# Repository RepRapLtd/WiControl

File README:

Wireless Home/Building Control System
=====================================

Adrian Bowyer
RepRap Ltd
https://reprapltd.com

Licence: GPL

This is a system for controlling devices in buildings (primarily, but not exclusively, heating; it will also do lighting and other things) with a web interface.  It is fully open-source and free.  The licence is the GPL.

There are two versions:

  1. Raspberry Pi + PanStamp in the directory PanStamp. This has been working for a few years, and is now frozen and will not be developed further.

  2. WiFi based on the ESP-8266 in the directory ESP-8266.  This is in development.

Both start with a php script that serves web pages where you can edit, for example, temperature profiles for individual rooms.  That data is saved in files on the server.

The ESP-8266s (or Pi) then get that data and decide(s) what to turn on and off.

More documentation needs to be written...

More importantly, security is minimal and needs to be properly implemented.

See also (for homemade solenoid valves): https://www.thingiverse.com/thing:3496770

WiControl - ESP-8266
====================

This version does everything that the PanStamp version did, but more simply and robustly (the robustness has nothing to do with the hardware change; the PanStamps are fine; it has to do with a simplification of the protocols and hardware).

This version of the system will also support Google Home and Amazon Echo/Alexa.

Some more instructions here would be a good idea...

WiControl - Raspberry Pi + PanStamp
===================================

This allows temperature profiles to be set for each individual room for all times of the day and every day of the week.

It can be controlled using a web browser from anywhere.

It uses Panstamps (http://www.panstamp.com/) for the individual rooms and a Raspberry Pi (https://www.raspberrypi.org/) as the main building controller.

This repository contains all the software and all the hardware designs.

One thing it lacks is full documentation, as I created it for my own use and I know how it works.  Sorry.

Installation:
-------------

On the Pi:

This assumes you have an out-of-the-box Raspberry Pi SD card with no extra software installed.

First set your local timezone:

$ sudo dpkg-reconfigure tzdata

You may want to change the default name of the Pi ("raspberrypi") to something more appropriate 
like "heatingcontrol".  To do that:

$ sudo nano /etc/hostname

That file contains a single name - the name of the Pi.  Change it to what you want, save the file, then reboot.

Change you password:

$ passwd

And enable ssh:

$ sudo raspi-config

Next install Apache and PHP:

$ sudo apt-get update
$ sudo apt-get install apache2 -y
$ sudo apt-get install php5 libapache2-mod-php5 -y

At this point it is a good idea to check that the webserver is now running.  In the URL address bar of a web browser on a PC or phone type

  myname.home/

where myname is the Pi's name that you created above (some networks need myname.local instead).  If you don't get anything type 

$ ifconfig

on the Pi.  This will tell you the Pi's IP address (something like 192.168.1.163).  Type that IP address into the web browser's URL bar.  You should see the default Apache/Debian server homepage.

Next install ftp:

$ sudo apt-get install ftp

And the ftp demon:

$ sudo apt-get install pure-ftpd

Create an ftp user (see https://www.raspberrypi.org/documentation/remote-access/ftp.md) called "upload" with access to the html directory:

$ sudo groupadd ftpgroup
$ sudo useradd ftpuser -g ftpgroup -s /sbin/nologin -d /dev/null
$ pushd /var/www/html/
$ sudo chown -R ftpuser:ftpgroup .
$ sudo pure-pw useradd upload -u ftpuser -g ftpgroup -d /var/www/html -m
[** You will be asked to create a password for the user upload at this point**]
$ sudo pure-pw mkdb
$ sudo ln -s /etc/pure-ftpd/conf/PureDB /etc/pure-ftpd/auth/60puredb
$ sudo service pure-ftpd restart
$ popd

You next need to install the heating software:

$ git clone https://github.com/RepRapLtd/WiControl.git
$ cd WiControl/PanStamp

Copy the control file:

$ cp run-heat-control.sample run-heat-control

and edit the file run-heat-control and replace the "zone-1"s with the name of the zone you want.

Copy the sending file:

$ cp sendtemps.sample sendtemps

and edit the sendtemps file to include the ftp password you set above and to change zone-1 to the name of your zone.

Backup the webserver's index file, and copy all the heating web files there and set permissions:

$ sudo mv /var/www/html/index.html /var/www/html/index.html.old
$ cd Web
$ sudo cp -r * /var/www/html
$ sudo chown -R ftpuser:ftpgroup /var/www/html
$ sudo chmod 666 /var/www/html/*.dat
$ sudo chmod 777 /var/www/html/zone-1-Profiles

Finally

$ sudo crontab -e

and add a line at the end like this:

* * * * * /home/pi/WiControl/run-heat-control

That will cause the shell script run-heat-control to be run once a minute.

On the PanStamps:

You can just about run the Arduino IDE on the Raspberry Pi, but it's probably better to
use a big serious computer to do this bit.  Install the Arduino IDE on your computer if
you haven't already got it:

https://www.arduino.cc/en/Main/Software

And clone the repository https://github.com/RepRapLtd/WiControl.git as you did on the Pi.

Load the arduino program in the folder Panstamp-control into the IDE.

At the head of the file Control.h set up your heating zones and device names and numbers.  Load 
this program into each device (e.g. boiler, radiator) on your heating system.

Running
-------

When it runs it creates a status file called Status.

$ cat Status

will tell you what your system last did.  If you

$ touch Log

then each time run-heat-control runs it will append the status
report to the end of itself, which keeps a history and is therefore
useful for debugging.

When you have finished debugging don't forget to

$ rm Log

otherwise it will eventually fill up the SD/disc...

Adrian Bowyer

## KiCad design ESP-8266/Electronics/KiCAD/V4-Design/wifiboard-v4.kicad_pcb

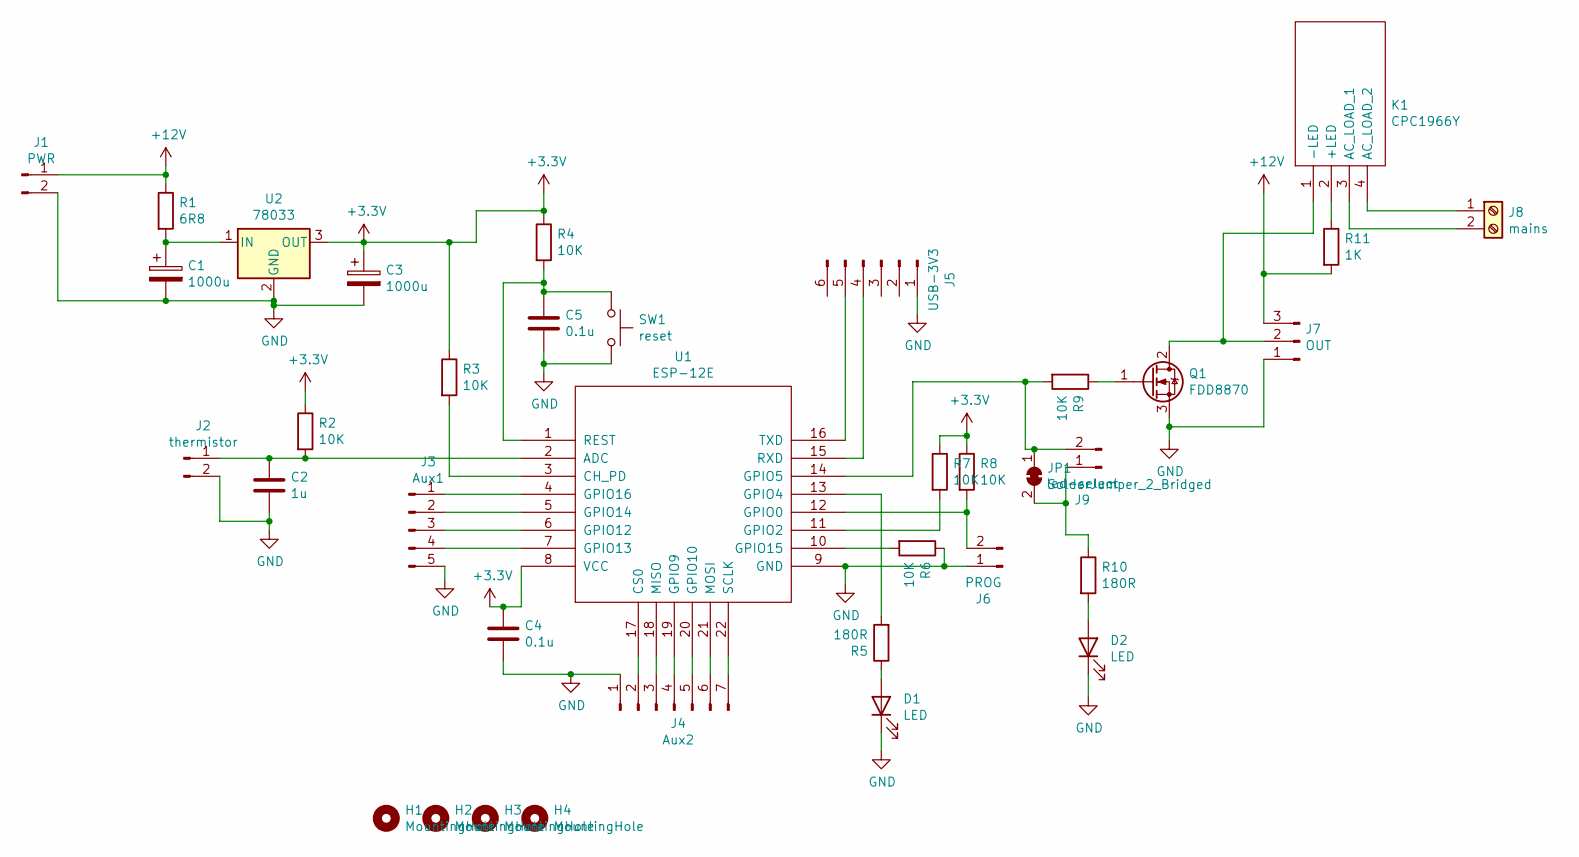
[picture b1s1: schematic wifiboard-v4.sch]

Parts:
C1, C3: 1000u; CP_Radial_D10.0mm_P5.00mm
C2: 1u; C_0805_2012Metric
C4, C5: 0.1u; C_0805_2012Metric
D1, D2: LED; LED_D3.0mm
H1, H2, H3, H4: MountingHole; MountingHole_2.5mm
J1: PWR; PinHeader_1x02_P2.54mm_Vertical
J2: thermistor; PinHeader_1x02_P2.54mm_Vertical
J3: Aux1; PinHeader_1x05_P2.54mm_Vertical
J4: Aux2; PinHeader_1x07_P2.54mm_Vertical
J5: USB-3V3; PinHeader_1x06_P2.54mm_Vertical
J6: PROG; PinHeader_1x02_P2.54mm_Vertical
J7: OUT; PinHeader_1x03_P2.54mm_Vertical
J8: mains; TerminalBlock_bornier-2_P5.08mm
J9: led-select; PinHeader_1x02_P2.54mm_Vertical
JP1: SolderJumper_2_Bridged; SolderJumper-2_P1.3mm_Bridged_RoundedPad1.0x1.5mm
K1: CPC1966Y; Manufacturer_Part_Number CPC1966Y; Mouser Part Number 849-CPC1966Y
Q1: FDD8870; TO-252-2
R1: 6R8; R_Axial_DIN0414_L11.9mm_D4.5mm_P15.24mm_Horizontal
R2, R3, R4, R6, R7, R8, R9: 10K; R_0805_2012Metric
R5, R10: 180R; R_0805_2012Metric
R11: 1K; R_0805_2012Metric
SW1: reset; SW_SPST_TL3342
U1: ESP-12E
U2: 78033; TO-252-2

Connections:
+3V3: C3.1, C4.1, R2.1, R3.1, R4.1, R7.1, R8.1, U1.8 (VCC), U2.3 (OUT)
+12V: J1.1, J7.3, R1.1, R11.2
GND: C1.2, C2.2, C3.2, C4.2, C5.2, D1.1 (K), D2.1 (K), J1.2, J2.2, J3.5, J4.1, J5.1, J6.1, J7.1, Q1.3 (S), R6.1, SW1.2, U1.9 (GND), U2.2 (GND)
unnamed: C1.1, R1.2, U2.1 (IN)
unnamed: C2.1, J2.1, R2.2, U1.2 (ADC)
unnamed: C5.1, R4.2, SW1.1, U1.1 (REST)
unnamed: D1.2 (A), R5.1
unnamed: D2.2 (A), R10.2
unnamed: J3.1, U1.4 (GPIO16)
unnamed: J3.2, U1.5 (GPIO14)
unnamed: J3.3, U1.6 (GPIO12)
unnamed: J3.4, U1.7 (GPIO13)
unnamed: J4.2, U1.17 (CS0)
unnamed: J4.3, U1.18 (MISO)
unnamed: J4.4, U1.19 (GPIO9)
unnamed: J4.5, U1.20 (GPIO10)
unnamed: J4.6, U1.21 (MOSI)
unnamed: J4.7, U1.22 (SCLK)
unnamed: J5.4, U1.15 (RXD)
unnamed: J5.5, U1.16 (TXD)
unnamed: J6.2, R8.2, U1.12 (GPIO0)
unnamed: J7.2, K1.1 (-LED), Q1.2 (D)
unnamed: J8.1, K1.4 (AC_LOAD_2)
unnamed: J8.2, K1.3 (AC_LOAD_1)
unnamed: J9.1, JP1.2 (B), R10.1
unnamed: J9.2, JP1.1 (A), R9.2, U1.14 (GPIO5)
unnamed: K1.2 (+LED), R11.1
unnamed: Q1.1 (G), R9.1
unnamed: R3.2, U1.3 (CH_PD)
unnamed: R5.2, U1.13 (GPIO4)
unnamed: R6.2, U1.10 (GPIO15)
unnamed: R7.2, U1.11 (GPIO2)

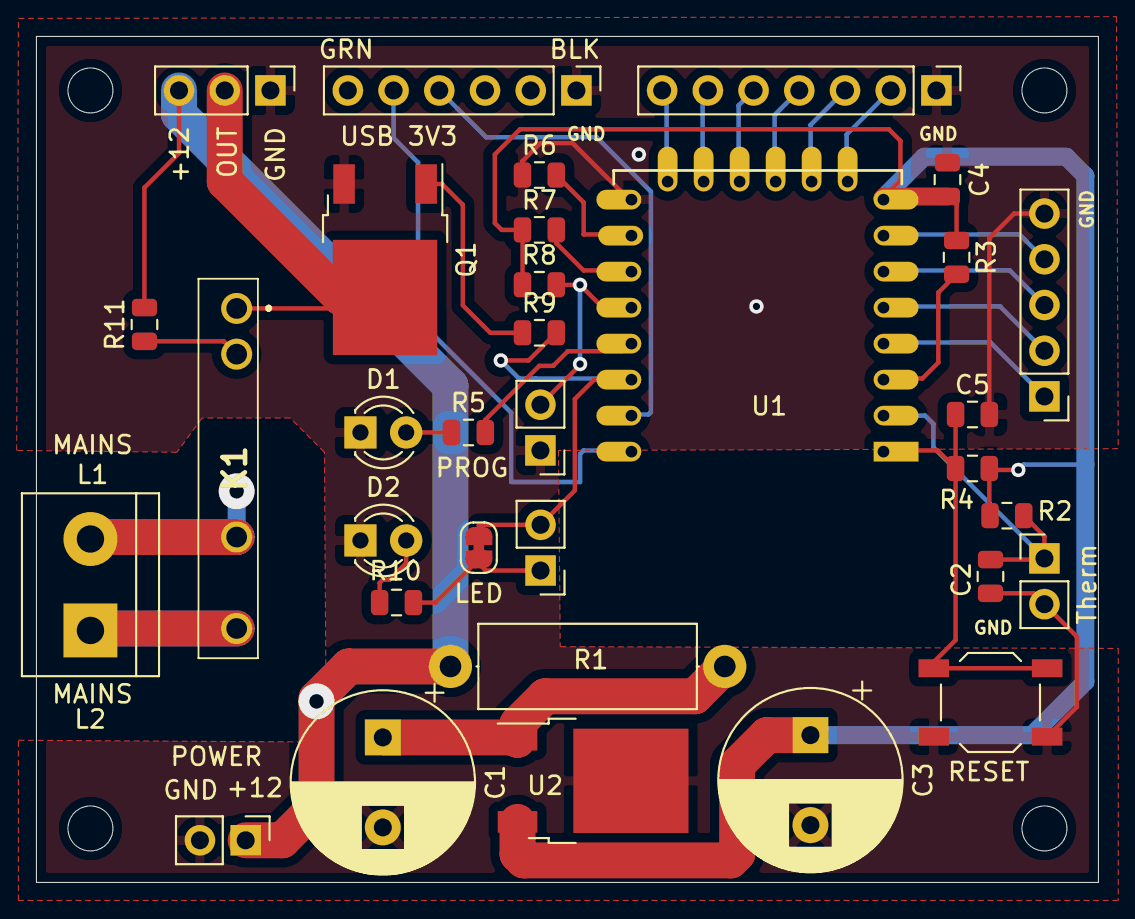
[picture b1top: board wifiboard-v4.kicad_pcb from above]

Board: 2 copper layers, 59.0 x 47.0 mm, 37 parts (0 on the bottom side), 32 nets.

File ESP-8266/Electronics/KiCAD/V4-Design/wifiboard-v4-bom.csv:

Reference, Value, Footprint, Datasheet, Arrow Part Number, Arrow Price/Stock, Description, Height, Manufacturer_Name, Manufacturer_Part_Number, Mouser Part Number, Mouser Price/Stock
"J5","USB-3V3","Connector_PinHeader_2.54mm:PinHeader_1x06_P2.54mm_Vertical","~"
"J3","Aux1","Connector_PinHeader_2.54mm:PinHeader_1x05_P2.54mm_Vertical","~"
"J4","Aux2","Connector_PinHeader_2.54mm:PinHeader_1x07_P2.54mm_Vertical","~"
"C4","0.1u","Capacitor_SMD:C_0805_2012Metric","~"
"J2","thermistor","Connector_PinHeader_2.54mm:PinHeader_1x02_P2.54mm_Vertical","~"
"C2","1u","Capacitor_SMD:C_0805_2012Metric","~"
"R2","10K","Resistor_SMD:R_0805_2012Metric","~"
"R3","10K","Resistor_SMD:R_0805_2012Metric","~"
"C5","0.1u","Capacitor_SMD:C_0805_2012Metric","~"
"R4","10K","Resistor_SMD:R_0805_2012Metric","~"
"SW1","reset","Button_Switch_SMD:SW_SPST_TL3342","~"
"R1","6R8","Resistor_THT:R_Axial_DIN0414_L11.9mm_D4.5mm_P15.24mm_Horizontal","~"
"J1","PWR","Connector_PinHeader_2.54mm:PinHeader_1x02_P2.54mm_Vertical","~"
"C1","1000u","Capacitor_THT:CP_Radial_D10.0mm_P5.00mm","~"
"C3","1000u","Capacitor_THT:CP_Radial_D10.0mm_P5.00mm","~"
"J6","PROG","Connector_PinHeader_2.54mm:PinHeader_1x02_P2.54mm_Vertical","~"
"R8","10K","Resistor_SMD:R_0805_2012Metric","~"
"R6","10K","Resistor_SMD:R_0805_2012Metric","~"
"R7","10K","Resistor_SMD:R_0805_2012Metric","~"
"R9","10K","Resistor_SMD:R_0805_2012Metric","~"
"D1","LED","LED_THT:LED_D3.0mm","~"
"R5","180R","Resistor_SMD:R_0805_2012Metric","~"
"U1","ESP-12E","esp-8266:ESP-12E","http://l0l.org.uk/2014/12/esp8266-modules-hardware-guide-got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"
"D2","LED","LED_THT:LED_D3.0mm","~"
"R10","180R","Resistor_SMD:R_0805_2012Metric","~"
"J7","OUT","Connector_PinHeader_2.54mm:PinHeader_1x03_P2.54mm_Vertical","~"
"K1","CPC1966Y","reprapltd-kicad:CPC1966Y","https://datasheet.datasheetarchive.com/originals/distributor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","CPC1966Y","https://www.arrow.com/en/products/cpc1966y/ixys","IXYS 3 A rms SPNO Solid State Relay, Zero Crossing, PCB Mount SCR, 240 V ac Maximum Load","10","LITTELFUSE","CPC1966Y","849-CPC1966Y","https://www.mouser.co.uk/ProductDetail/IXYS-Integrated-Circu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"
"R11","1K","Resistor_SMD:R_0805_2012Metric","~"
"J8","mains","TerminalBlock:TerminalBlock_bornier-2_P5.08mm","~"
"Q1","FDD8870","Package_TO_SOT_SMD:TO-252-2","http://www.jaolen.com/images/pdf/QM6006D.pdf"
"H4","MountingHole","MountingHole:MountingHole_2.5mm","~"
"H3","MountingHole","MountingHole:MountingHole_2.5mm","~"
"H2","MountingHole","MountingHole:MountingHole_2.5mm","~"
"H1","MountingHole","MountingHole:MountingHole_2.5mm","~"
"J9","led-select","Connector_PinHeader_2.54mm:PinHeader_1x02_P2.54mm_Vertical","~"
"U2","78033","Package_TO_SOT_SMD:TO-252-2","http://www.st.com/content/ccc/resource/technical/document/da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"
"JP1","SolderJumper_2_Bridged","Jumper:SolderJumper-2_P1.3mm_Bridged_RoundedPad1.0x1.5mm","~"

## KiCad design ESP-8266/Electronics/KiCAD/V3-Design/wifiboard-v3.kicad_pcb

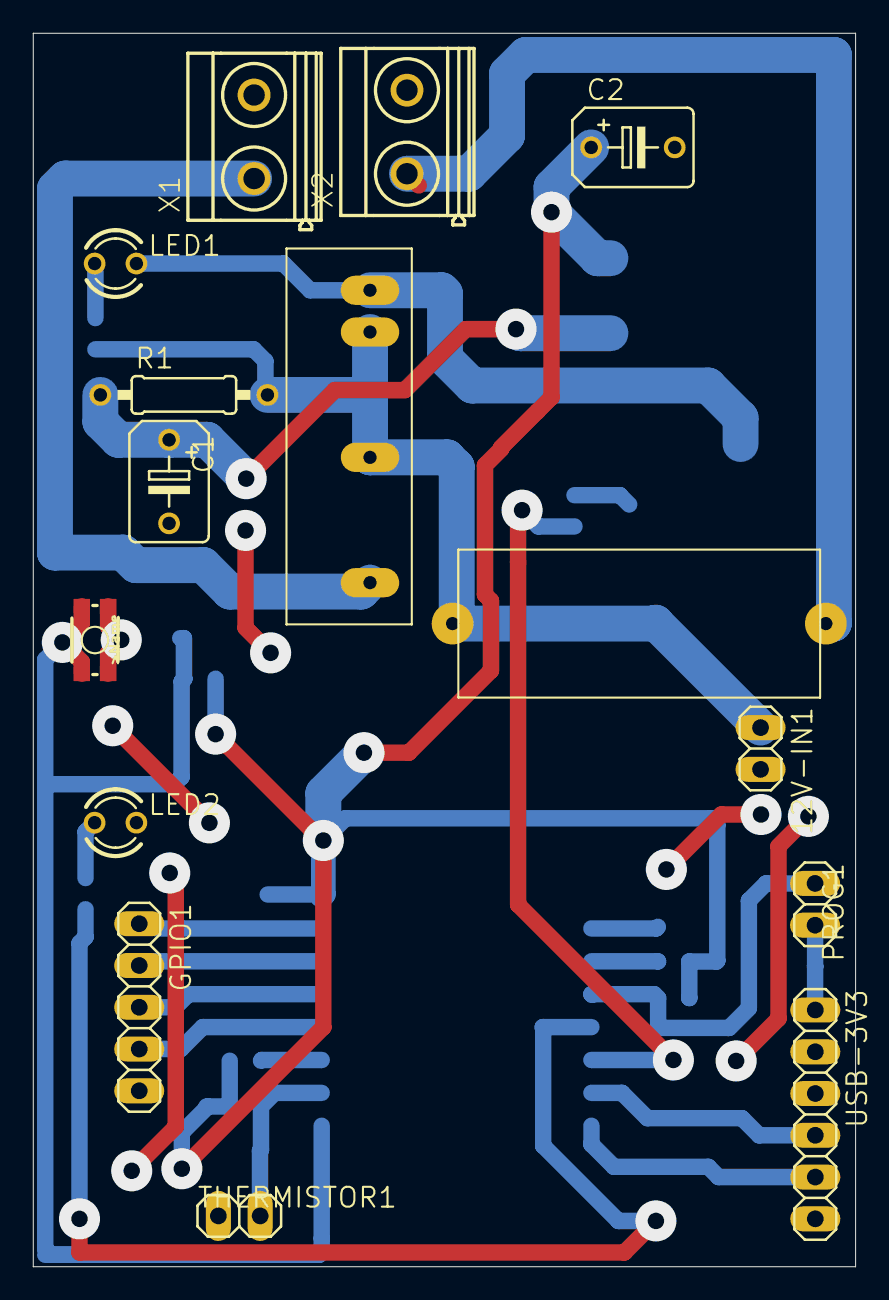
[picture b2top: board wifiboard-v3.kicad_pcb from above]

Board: 2 copper layers, 50.0 x 75.0 mm, 30 parts (0 on the bottom side), 24 nets.

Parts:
12V-IN1: PINHD-1X2; 1X02
C1, C2: 1000uF; B45181B
C3: 1uF; C0805
C5, C6: 0.1u; C0805
FUSE1: FUSE
GPIO1: PINHD-1X5; 1X05
IC2: 78033AF; TO252
LED1, LED2: LED3MM
PROG1: PINHD-1X2; 1X02
Q1: FDD8870; DPAK
R1: 6R8; 0207_10
R2, R3: 10K; M0805
R4, R5, R6, R7, R8: 10K; R0805
R9: 1K; R0805
R10: 180R; R0805
RESET1: TACTILE_SWITCH_SMD_4.6X2.8MM
RLA1: OMRON-G6DN; OMRON-G6DN-1A
THERMISTOR1: PINHD-1X2; 1X02
U2: ESP12ESMD; ESP12E-SMD
USB-3V3: PINHD-1X6; 1X06
X1: AC-N; MKDSN1,5_2-5,08
X2: AC-L; MKDSN1,5_2-5,08

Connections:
+3V3: C2.+, C5.1, IC2.2, R2.1, R4.2, R5.2, R7.2, R8.2, U2.VCC
+12V: 12V-IN1.1, FUSE1.P$1, R1.2, R9.2, RLA1.P$2, RLA1.P$3
GND: 12V-IN1.2, C1.-, C2.-, C3.2, C5.2, C6.2, GPIO1.5, IC2.3, LED2.K, PROG1.2, Q1.3, R6.1, RESET1.3, RESET1.4, THERMISTOR1.1, U2.GND, USB-3V3.1, X1.2, X2.2
unnamed: C1.+, IC2.1, R1.1
unnamed: C3.1, R2.2, THERMISTOR1.2, U2.ADC
unnamed: C6.1, R4.1, RESET1.1, RESET1.2, U2.RESET
unnamed: FUSE1.P$2, X2.1
unnamed: GPIO1.1, U2.GPIO13
unnamed: GPIO1.2, U2.GPIO12
unnamed: GPIO1.3, U2.GPIO14
unnamed: GPIO1.4, U2.GPIO16
unnamed: LED1.A, R9.1
unnamed: LED1.K, Q1.4, RLA1.P$1
unnamed: LED2.A, R10.1
unnamed: PROG1.1, R5.1, U2.GPIO0
unnamed: Q1.1, R3.1
unnamed: R3.2, U2.GPIO5
unnamed: R6.2, U2.GPIO15
unnamed: R7.1, U2.CH_PD
unnamed: R8.1, U2.GPIO2
unnamed: R10.2, U2.GPIO4
unnamed: RLA1.P$4, X1.1
unnamed: U2.RXD0, USB-3V3.4
unnamed: U2.TXD0, USB-3V3.5

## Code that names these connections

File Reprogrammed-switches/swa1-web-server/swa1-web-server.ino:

/*

SWA1 Smart Switch Web Server

This turns a SWA1 smart switch into a web server on your network. You can
then load the page it serves in a browser on your PC or phone and turn 
the switch on or off from that page.

RepRap Ltd
https://reprapltd.com


Written by GPT4 (code) and Adrian Bowyer (comments)

3 May 2024

Licence: GPL


**** UNPLUG THE SMART SWITCH FROM THE MAINS FOR ALL BUT THE VERY END OF THIS. ****


Select "Generic ESP8266 Module" from the Arduino IDE Boards menu.

Open the Arduino IDE serial monitor and set the speed to 74880 baud.

Edit the code below to put your network's WiFi SSID and password in.

Dismantle the smart switch (5 Phillips screws on mine). 

The SWA1 Smart Switch has an ESP8266 internally which you can access
through a 5-pin connector on its PCB. (You may have to solder that connector in - it's 
not fitted on all devices.)

The pins are (counting pin 1 as the pin nearest the edge of the PCB):

Pin   GPIO    Function

1     3       Rx (recieve)
2     1       Tx (transmit)
3     -       GND (0v)
4     0       hold 0 to program on power up
5     -       Vdd (+3v3)

Internally, the LED is on GPIO4, the mains relay is on GPIO5 and the push button
grounds GPIO13.   

To program it from the Arduino IDE you will need a TTL-232R-3v3 USB cable.

Connect that as follows

SWA1      TTL-232R-3v3

Rx        Tx (Orange)
Tx        Rx (Yellow)
GND       GND (Black)
GPIO0     RTS (Green)
Vdd       3v3 (Red)

Puting a normally-closed push button in the power (3v3) line will make things
easier. You have to cycle the power as the Arduino IDE starts to program the device.
The sequence is that the IDE compiles the code then pulls RTS low. The ESP8266 has
to be rebooted then to put it in programming mode, so you push the switch for a second
when the IDE says it's trying to connect. You won't get the timing right every go, but it 
usually works. If you don't catch it, the ESP8266 just retains whatever firmware was in
it before. Try again.

When the IDE has completely finished programming the device (don't do this too early) you can
can reboot the ESP8266 by cycling its power again. It should then give a series of dots as it connects 
to your network and then tell you the IP address it's been allocated.

Put that IP address into a web browser and you will get a page that allows you to
turn the switch on and off. Pushing the button on the front of the switch achieves
the same.

Tell your internet hub to always use that IP address for the device then put it
all back together. Plug it into a socket and you have a web-page-controlled mains switch.


*/


#include <ESP8266WiFi.h>
#include <ESP8266WebServer.h>

const char* ssid = "MY_SSID";
const char* password = "my_password";

ESP8266WebServer server(80);

// Pin definitions
const int relayPin = 5;
const int buttonPin = 13;
const int ledPin = 4;

// Variable to store the relay state
bool relayState = false;

void setup() {
  Serial.begin(74880);
  pinMode(relayPin, OUTPUT);
  pinMode(buttonPin, INPUT_PULLUP); // Set button input mode
  pinMode(ledPin, OUTPUT);

  // Initialize relay and LED state
  digitalWrite(relayPin, relayState);
  digitalWrite(ledPin, relayState);

  WiFi.begin(ssid, password);
  Serial.println("");

  // Wait for connection
  while (WiFi.status() != WL_CONNECTED) {
    delay(500);
    Serial.print(".");
  }
  Serial.println("");
  Serial.print("Connected to ");
  Serial.println(ssid);
  Serial.print("IP address: ");
  Serial.println(WiFi.localIP());

  // Define server routes
  server.on("/", handleRoot);
  server.on("/toggle", handleToggle);

  server.begin();
  Serial.println("HTTP server started");
}

void loop() {
  server.handleClient();
  checkButton();
}

void checkButton() {
  static bool lastButtonState = HIGH;
  bool currentButtonState = digitalRead(buttonPin);
  if (lastButtonState == HIGH && currentButtonState == LOW) {
    // Button is pressed; toggle the relay
    relayState = !relayState;
    digitalWrite(relayPin, relayState);
    digitalWrite(ledPin, relayState);
  }
  lastButtonState = currentButtonState;
}

void handleRoot() {
  String page = "<html><head><title>ESP8266 Relay Control</title></head><body><h1>Relay Control</h1><p><a href=\"/toggle\"><button>Toggle Relay</button></a></p></body></html>";
  server.send(200, "text/html", page);
}

void handleToggle() {
  relayState = !relayState;
  digitalWrite(relayPin, relayState);
  digitalWrite(ledPin, relayState);
  // Redirect back to the root page
  server.sendHeader("Location", "/", true);
  server.send(302, "text/plain", "");
}

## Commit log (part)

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2013-10-27 Panstamp wireless control system - first commit.
2013-10-29 Minor tidying.
2013-11-02 Simple command interpreter added.
2013-11-04 Adding more commands...
2013-11-06 Bug: received message never acted on...
2013-11-08 First working version.
2013-11-15 Thermistor parameters corrected.
2013-11-17 Sketch of controller PCB started in Eagle.
2013-11-17 First version of PCB complete.
2013-11-17 Final (?) PCB design.
2013-11-17 Tidied final (?) PCB design.
2013-11-19 Extras added to PCB, + tidying.
2013-11-19 More tidying...
2013-12-07 Smaller 3v3 reg used, that can also stand 20V.
2013-12-19 Added Gerber files.
2014-01-04 First test of PCB. It works!
2014-01-07 BoM spreadsheeet added.
2014-01-07 Case design added.
2014-01-11 Code tidying.
2014-01-14 Starting work on the Host software.
2014-01-14 More work on the Host software.
2014-01-15 More host s/w...
2014-01-16 More host s/w
2014-01-18 First working version of the host control software.
2014-01-18 Minor improvements to output from host.
2014-01-20 Now with retries.
2014-01-30 Watchdog reset added at 30 secs. Timer is reset if a radio message arrives.
2014-01-31 Watchdog timer added.
2014-02-01 Tidying...
2014-02-06 usleep(2000) added to wait for incoming USB bytes on the host s/w so it doesn't hog CPU cycles in a tight loop waiting for bytes (which will be buffered anyway).
2014-05-12 Test trivial modification
2014-06-14 Added code to invert temperature behaviour to allow the control of cooling devices. Added code to allow the sensor Panstamp number to be different from the switch Panstamp number. Temperature profile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
2014-06-14 First version of the web interface PHP written.
2014-07-27 Case design improved and made partly parametric.
2014-07-29 Timeout on wget added.
2014-07-29 Raspberry Pi Version
2014-07-31 Libserial for R Pi added. Presence of Log file is now used to decide whether to append to it or to throw the output away.
2014-08-19 RGB LED lighting control added.
2014-08-24 U floor added.
2014-08-24 Proper delay timing added.
2014-08-25 Named location added to each Panstamp.
2014-08-25 Heating control program now allows multiple devices per room and temperature.
2014-08-25 String limit changed to *. All seems to work...
2014-08-25 Firmware built with make outside Eclipse.
2014-08-25 Final ??? Version...
2014-08-28 Control now configured for latest Eclipse Arduino and arduino-1.5.7
2014-08-28 Fixed libserial for the pi.
2014-08-31 Host code tidying - Device class used throughout. Delays added in poll loops.
2014-09-13 Starting to fit in the main house...
2014-09-13 Gradual LED fade added.
2014-09-26 Heatprofile bug squashed (deviceCount too big).
2014-09-26 This time with the correct run_heat_control...
2014-10-07 STatus and Log implemented.
2014-10-12 Time and date commands added to control firmware.
2014-10-12 On/Off switching made more robust.
2014-10-12 Added time setting to host software.
2014-10-12 Ignore updated to remove shell script from commits
2014-10-12 Sample shell script added.
2014-10-12 Now prints the time from the Panstamp.
2014-10-12 Now with daylight saving...
2014-10-12 Correct printf format now used for sending unsigned long time...
2014-10-17 Added link to pi ntp stuff.
2014-10-18 File tidying plus better README.md file.
2015-01-16 Good settings for A&C saved.
2015-02-08 Proper web interface... WIP
2015-02-08 Example shell script...
2015-02-14 New Webform just about complete
2015-02-15 need to sudo apt-get install gettext
2015-02-22 Shellscript amended to put absolute path for wget in.
2015-02-22 Removed unwanted files
2015-02-22 Removed unwanted files.
2015-03-01 Temperature log file upgraded to have set temps in as well as room temps, and a heating on/off flag.
2015-03-26 Getting Eclipse compiling the Panstamp program again...
2015-08-28 README file improved...
2015-08-28 README made more legible
2015-08-28 Again readability...
2015-08-28 Readability
2015-08-29 Further README corrections
2015-09-01 Fixed problem with wput compilation
2015-09-20 Host now reads the old temperature profile and uses those temps if wireless to a device fails.
2015-10-02 Script updated to record stderr as well as stdout.
2015-10-15 Reverting to adrianbowyer.net
2016-01-17 Bug in Switch class fixed.
2016-01-31 Improving Panstamp debugging. WIP.
2016-03-15 Fixed -10 temp bug
2016-03-15 Pi version
2016-03-15 removed surplus
2016-07-28 Bringing in-line with latest version
2016-07-28 Fixed temperature rounding and transmission as 10* int.
2016-07-28 Fixed (I think) watchdog.
2016-07-28 Fixed README
2016-07-29 Setting up classic Makefile for Pi-control
2016-07-30 New working version of Pi host program.
2016-07-31 Changed output to make Log more readable when ther is a timeout.
2016-07-31 This time with correct logic...
2016-07-31 Added code to check for non-responding devices.
2016-07-31 Minor tidying
2016-09-12 Fixed dud start of winter (month 8!).
2016-11-03 Updated README and added .gitignore (not before time...).
2016-11-03 Removed edit backup files.
2016-11-03 More README...
2016-11-03 File tidying and adding latest server side web code.
2016-11-03 Added code to run server side on local server.
2016-11-04 Full local control now working
2016-11-04 Combining server and controller on the same Pi.
2016-11-06 Finalising and tidying local server version. Updating README.
2016-11-06 Further tidying...
2017-01-31 More README updating
2017-02-05 Started work on Networked/WiFi replacement for PanStamps.
2017-06-05 WeMos design added. Not final (need to replace 78L05 with 7805 to get enough current).
2017-11-14 Working on the WiFi/ESP-8266 version...
2017-12-04 Tidied up wifi files. Added WiFi FreeCAD case.
2017-12-07 Improved PCB design and casing.
2017-12-29 Started work on the WiFi client for the domestic control system.
2017-12-31 WIP - WiFi controller
2018-01-01 First version of the ESP8266 software.
2018-01-02 More work on the s/w...
2018-01-03 Nearly finished the server .php script
2018-01-04 First working (?) version of the WiFi controller php program.
2018-01-05 Debugging the WiFi PHP script.
2018-01-08 Improved .PHP control program
2018-02-09 Finalising (?) the ESP-8266 code and the .php script.
2018-02-15 Remote server working. Backup server added to Arduino code (doesn't yet work...)
2018-02-21 Minor improvements to debugging behaviour.
2018-03-15 heating.php improved to check that times monotonically increase throughout the day.
    Various bits of experimental WiFi electronics added.
2018-03-16 More correctness checking in heating.php
2018-04-12 Simple web monitoring added to the thermostat program.
2018-04-13 Improvements to thermostat
2018-04-17 Tidying ControlNode for the WiFi heating system.
2018-05-01 controllednode.php fixed to deal with timezone (maybe summer time too?)
2018-05-01 This time with the right filename...
2018-05-03 Improving the box design. Also fixed daylight saving in controllednode.php
2018-07-17 Gerbers for WiFi PCB done.
2018-07-18 WiFi PCB as ordered.
2018-09-04 Test changes; none significant.
2018-09-05 New version of the WiFi client end firmware written, ControlledNode2. Seems to work...
2018-09-06 Parts spreadsheet set up. PHP changed to make summertime work.
2018-09-07 Improved case design.
2018-09-07 More robust version of post.php
2018-09-07 Controlnode programs (these need new names...) modified to set and use the switching delays.
2018-09-10 Adding multiple loads to the control firmware. W.I.P.
2018-09-10 Load class in WiFi firmware now compiles. More W.I.P.
2018-09-10 Multi-device controlling firmware works...
2018-09-11 ESP8266-12 pinouts added to HomeControlFirmware.h
2018-09-12 Improved README...
2018-09-12 File tidying.
2018-09-12 Now with the right names...
2018-09-12 Increasing the number of mains adapters that can be incorporated.
2018-09-18 New power-supply case added. Tidied file structure. More comments in software.
2018-09-25 Set temp offset to 0. Added complete parts list.
2018-11-07 Firmware now reports internal status, and connecting to WiFi.
2018-11-07 More TODOs added.
2018-11-08 .php script improved to detect and report dead devices.
2018-11-29 WIP: Adding a class to record and recover strings from flash memory so that the device can be configured on the fly and remember that when it's powered off then on again.
2018-11-29 Sm. bug spotted and fixed.
2018-11-30 Saving and loading settings to/from flash (seems to be) working.
2018-12-02 Fully flash-configurable version of the client firmware.
2018-12-12 Client prompt early in boot.
2018-12-13 Temperature offset added to the configurable variables.
2019-01-11 Added image of schematic
2019-01-23 WiFi works. Horay!
2019-01-30 File reorganising
2019-02-26 New branch.
    Started work on Sally's idea of having each client just identified by a number,
    along with a table on the server that matches numbers to locations.
    New client ESP8266 code compiles...
2019-02-28 First full working version of Sally's idea.
2019-03-04 Data logging added to the new system.
2019-03-09 Improved lid design with connector.
2019-07-01 Small bug in scontrollednode.php fixed.
2019-08-15 Added file-touch .php script heatsource.php to allow the old system to turn on a boiler in the new system.
2019-08-15 Added short bit to shell script to turn boiler in the new system on from the old system.
2019-09-24 Sorted out update of globals.php
2019-09-25 Fixed small bug in the .php script; updated URLs for home system.
2019-09-25 Added example HTTP request in comment
2019-10-02 Better globals.php...
2019-10-02 Shell script added to test if new system has requested the boiler to be on and to relay that to the master server.
2019-10-03 Updated units.dat
2019-10-03 Multi controller for underfloor added to units
2019-10-04 Tidied Client software.
2019-10-04 Tidying HomeControlFirmware.h
2019-10-18 Fixing (ish) problem with multiple loads. Can't seem to have more than 3, though there's 50K of heap. ???
2019-10-26 Retained crimp plug for valve connection added to design.
2019-11-14 Fixing transparency, but there seems to be a bug in the screw corner retainers...
2019-11-14 Fixed fault in walls design. Salvaged from previous commit.
2019-11-19 scontrollednode.php improved - CSV logfile generation added; more sensible time and date formats in output.
2019-11-19 Updating globals.php
2019-11-30 Removing error exits and putting messages in debug string.
2019-11-30 Updated template for local wifi .H file
2019-11-30 Removed error exits from scontrollednode.php and replaced with reporting error string.
2019-11-30 error string added to globals.
2019-11-30 Turning logging on and getting the log from the web interface W.I.P.
2019-12-01 Web control of data logging implemented.
2020-04-25 Added link to 3D printed motorised valve.
2020-05-11 Updated php script because of !*$**!! depricated message suddenly introduced
2020-09-29 Deprecated usages of parse_str removed from PHP files.
2020-10-19 Added code to output Unix times into the logs.
2020-12-06 Set off temperature from 10C to 5C in scontrollnode.php
2021-02-26 Keeping repo up to date with online version.
2021-04-27 Sally's WIP on new PCB design.
2021-05-06 Tidying files; previous...
2021-06-18 Now saves configuration in EEPROM (if it works...)
2021-06-18 Debugging WIP...
2021-06-21 Updated firmware with interactive setup.
2021-07-10 Updated deprecated wifi code.
2021-07-11 Added erase flash option on boot in debug mode.
2022-01-11 Added hysterisis to the system's ON/OFF with temperature.
2022-01-12 Correcting units.dat
2022-01-28 Trying to start V4 PCB. Not working yet.
2022-01-31 Redoing V4 electronics to make it fully KiCAD.
2022-02-01 V4 schematic complete (?)...
2022-02-02 Components positioned on PCB.
2022-02-03 SB & AB PCB layout
2022-02-09 PCB sent for trial production.
2022-02-14 Double patress box front plate design first complete design.
2022-02-15 Improved patress front plate design.
2022-02-21 This time with the right size for the PCB...
2022-05-20 Keeping things up to date.
2022-07-06 PCB modified to accommodate relay as well as opto-SCR. GERBERS need to be updated.
2024-05-03 Added stuff on hacking existing smart switches, specifically SWA1.
2024-05-03 Comments updated.
2024-05-03 More comments
2024-05-03 cpmments...
